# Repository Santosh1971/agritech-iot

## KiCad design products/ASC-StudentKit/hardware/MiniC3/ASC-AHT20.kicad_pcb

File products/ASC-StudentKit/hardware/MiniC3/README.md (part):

# ASC Mini-C3 rev B: the low-cost Mini, shared with FG1

This is the cost-down Mini for the ASC Student Kit (2026-10-10). The same board is meant to become the next **FG1 (FlowGuard)**: it has FG1's flow input, relay, RTC and LEDs. It does not replace rev A (`../Mini`, ESP32-S3 module, 97 × 47 mm).

Two boards share one 100 × 100 order:

| Board | Size | What it is |
|---|---|---|
| **ASC-MiniC3** | 48 × 44 mm | Carrier for a plug-in ESP32-C3 Super Mini. It has a flow input, a 5 V pump driver, a 230 V relay, a DS1307 RTC, I2C and AUX terminals and four LEDs. |
| **ASC-AHT20** | 48 × 6 mm | A T/RH "sensor stick" on a 4-core cable, so the sensor sits outside the box and students can breathe on it |

**The panel (`fab/ASC-MiniC3-panel-gerbers.zip`, 98 × 98 mm, order this one):**
- It holds 4 Minis (2 × 2) and **2 sticks** underneath. FG1 builds don't need a stick.
- **No V-cut.** JLC charges extra for V-cut, so WhyPCB asked for routed slots instead.
- The boards are separated by **2 mm routed slots**, drawn as closed cut-outs in the board outline.
- The slots stop short at the panel edges and around the slot crossings, leaving small **plain tabs**: about 2 mm at the edges and 5 mm at the crossings.
- **No mouse bites:** WhyPCB says JLC may not accept them. To set them back, change `MOUSE_BITES` in `tools/panel.py`. Break the tabs with pliers or a nibbler and file the stubs flush.
- The zip also carries `ASC-MiniC3-panel-drawing.pdf` and `PANEL-README.txt` for the fab.
- Copper keeps ≥ 0.4 mm from every edge.
- **Price** (WhyPCB): ₹1,500 for 5 panels or ₹2,000 for 10, which is ₹50 per Mini at 10 panels. 98 × 98 stays inside their 100 × 100 price; they also accept up to 102 × 100.

## Status

| Item | State |
|---|---|
| Schematics | Both are generated from `tools/design.py` and `tools/design_aht20.py`. **ERC: 0 errors, 0 warnings** on both. |
| PCBs | Both are routed (Freerouting) with zones filled. **DRC at every severity: 0 violations, 0 unconnected, schematic parity clean** on both (kicad-cli 9.0.7). The panel's DRC shows 0 errors. |
| 230 V | **5.3 mm** measured from relay copper to anything else. The DRC rule in `ASC-MiniC3.kicad_dru` requires ≥ 5 mm. Inside the relay, coil and contacts are 9.6 mm apart. |
| Fab | Panel, Mini and stick Gerbers. JLC BOM/CPL for each board and for the panel (unique designators R1_1 … R1_4). Schematic PDFs, 1:1 prints and renders. Run `tools/fab.sh` to regenerate. |
| Costing | `costing.csv`: board plus stick about ₹267, full kit about ₹1,026 (IP-65-26, YF-S401 at ₹230, HF46F at ₹42, 3 standoffs) |
| Mounting | 3 × 4.2 mm holes, arranged in a triangle, for 5 mm nylon reverse-mount snap standoffs (Probots PRO5803, ₹9.40 at 50+). Each standoff's flat base sticks to the box floor with double-sided foam tape; the snap head goes through the PCB hole. This works in any box with a flat floor; the box's own bosses are not used. Enclosure: REI IP-65-26 (90 × 58 × 44). |

## 3D models

Our own parts have no 3D models in KiCad's library (the Phoenix terminals, the MSTBVA header and the JST-XH do). `tools/gen_3d.py` writes simple coloured STEP models for them into `ASC.3dshapes/` (boxes and cylinders sized from the datasheets):
- the Super Mini on its sockets;
- the tabbed CR2032 and the HF46F relay;
- the AHT20 and the snap standoffs (the standoffs show below the board).

`tools/apply_3d.py` attaches them to the routed boards without re-routing; `gen_pcb.py` and `panel.py` attach them automatically. `fab/ASC-MiniC3.step` and `fab/ASC-AHT20.step` are full board assemblies, for checking the fit in the enclosure.

## Pin map (ESP32-C3 Super Mini)

| GPIO | Function | Notes |
|---|---|---|
| IO0, IO1 | AUX A0, A1 | ADC1 inputs |
| IO3 | PUMP | ULN2003A channels 1 + 2 in parallel (about 0.9 V drop, so ~4 V at the pump). Off through reset. |
| IO4 | AUX D | 10 k pull-up. For DHT11/22 or a DS18B20 probe. |
| IO5 | FLOW | YF-S401 (5880 pulses per litre) or YF-S201 (450 per litre). Level-shifted by D2 + R6. |
| IO6, IO7 | SDA, SCL | DS1307 (0x68) and AHT20 (0x38). 4.7 k pull-ups to 3V3. |
| IO10 | STATUS LED | FG1 uses it as the WiFi/status LED |
| IO20 | RELAY | ULN2003A channel 3. This pin is UART0 RX, an input at boot, so the relay stays off while the board boots. ULN2003A inputs 4–7 are grounded, outputs 4–7 free. |
| IO2, IO8, IO9, IO21 | free | IO2/8/9 are strapping pins (IO8 = module LED, IO9 = BOOT). IO21 is UART0 TX. |

## Connectors

| Ref | Connector | Pins |
|---|---|---|
| J5 | I2C, 4-pole 3.5 mm screw terminal (top edge) | 3V3, GND, SCL, SDA. This is the AHT20 stick's order and the usual VIN GND SCL SDA module order. |
| J4 | FLOW (top right): one footprint, fit **either** a JST-XH 3-pin header (student bench: takes the YF-S401 plug) **or** a 3-pole 3.5 mm screw terminal (FG1 / field: long cable). | 5V (red), GND (black), SIG (yellow); silkscreen reads S G 5V, left to right |
| J3 | AUX, 5-pole 3.5 mm screw terminal (bottom edge) | 3V3, D, A0, A1, GND |
| J1 | PUMP, 2-pole 3.5 mm screw terminal (bottom edge) | P+ (5 V), P− (low side) |
| J6 | RELAY 230 V, pluggable 5.08 mm 2-pole MSTBVA header + plug (bottom right), the same family as FG1's relay connector | NO, COM. HF46F, 5 A 250 VAC, for a pump contactor coil. |

## Assembly markings (for hand soldering)

House style, as on the WPC and FG1 boards:
- **Labels:** every part has its reference and value on the top silkscreen: `R3 1K`, `R5 470E`, `U3 ULN2003`, `C1 220U`, `D3 YEL` and so on. R8 and R9 share one label, `R8 R9 4K7`.
- **Big parts:** the relay and coin-cell labels sit inside their outlines, where the part goes.
- **Pin 1:** a **1** marks pin 1 of each IC (U2 DS1307, U3 ULN2003, the AHT20).
- **Anodes:** a **+** marks the anode of every LED and of D2.
- **LED colours:** PUMP and RLY yellow, STATUS red, FLOW yellow-green. FLOW runs from 3.3 V, too low for an emerald green LED. The Super Mini's own blue LED (GPIO8) is the WiFi-status LED in firmware. The electrolytic and the coin cell carry their own + marks.
- **LED size:** the LEDs are **1206** (bigger pads, as on WPC).
- **Back:** "ASC Mini-C3 rev B / Agri Sensors and Controls Oct 2026".

`gen_pcb.py` places the labels automatically, clear of pads, part bodies and each other (`ASSEMBLY_VALUE`, `LABEL_INSIDE` and `MARKS` in the design file). The LED block is laid out by hand in `silk()`.

## LEDs (seen through the clear lid)

| LED | How it's driven |
|---|---|
| PUMP (red) | Hardware: on the pump driver |
| FLOW (yellow) | Hardware: blinks with every flow pulse |
| STATUS (green) | GPIO10 |
| RELAY (blue) | Hardware: across the relay coil |

## Moving FG1 onto this board

1. **Firmware.** FG1 runs on a classic ESP32 today (`esp32dev`). It needs a C3 build with these pins: RELAY IO20, FLOW IO5, I2C IO6/IO7, status LED IO10.
2. **Flow LED.** It no longer needs a GPIO, so FG1's `FLOW_SENSOR_LED_PIN` goes away.
3. **Flow sensor.** Set `DEFAULT_PULSES_PER_LITER` to suit the sensor: 450 for a YF-S201, 5880 for a YF-S401.
4. **Power.** In the field, FG1 runs from a 5 V / 1 A USB-C charger plugged into the Super Mini.
5. **Relay.** The relay is an HF46F (5 A), not FG1's SRD (10 A). That is ample for a contactor coil. The SRD's COM pin sits between its two coil pins, which made 5 mm clearance impossible on a 48 mm board.

## Check before ordering

1. **Super Mini footprint.** Print `fab/ASC-MiniC3-print-1to1.pdf` at 100 % and lay a real Super Mini on it. The rows should be 15.24 mm apart. The silkscreen marks IO5 and 5V at the USB end and IO21 and IO0 at the far end, so a mirrored module is easy to see.
2. **Tabbed CR2032.** The two + legs are 15.2 mm apart. The − leg offset of 4.0 mm is a guess, so measure one cell.
   - **Alternative:** a replaceable cell in a CR2032 holder ([Rajiv Electronics](https://rajivelectronics.com/product/cr2032-3v-pcb-mount-vertical-battery-holder), ₹11.80).
   - The Rajiv holder (photo, SKU RBH-2) is a vertical holder with **3 pins**. A different holder's datasheet shows 2 pins 20.0 mm apart, so the layout varies by maker.
   - Its pin positions may or may not match the tabbed cell's pads. **Measure a sample before ordering.**
   - If they differ, its pads can be added next to the tabbed cell's, the same way the flow connector takes either part.
3. **YF-S401 plug order.** The board expects 5V (red) on pin 1, GND (black) in the middle and SIG (yellow) on pin 3. This follows AM Electronics' listing and photo. Check one plug: red must land on the pin next to the 5V label.
4. **HF46F footprint.** It is the same footprint as rev A (Hongfa datasheet). Push a real relay through a 1:1 print.
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
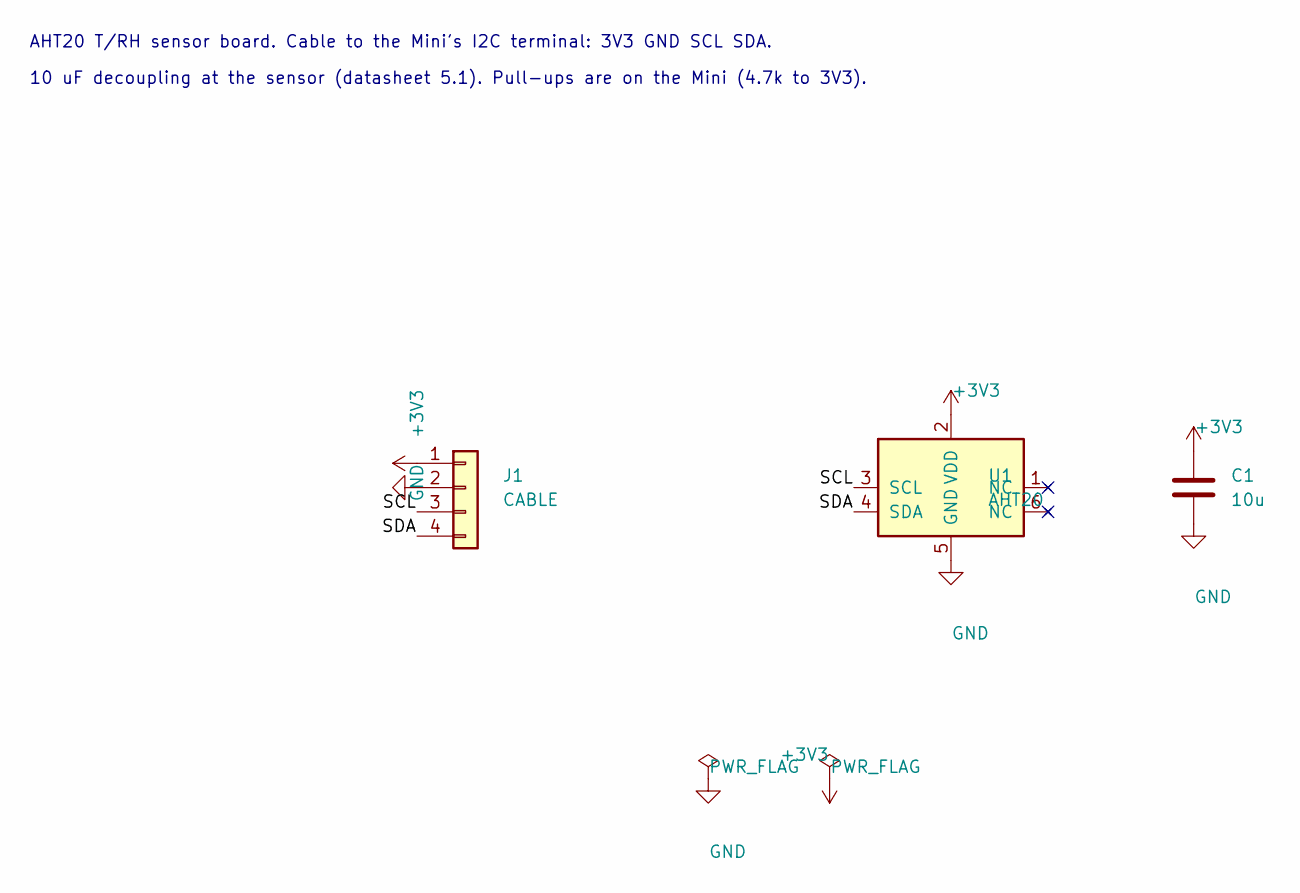
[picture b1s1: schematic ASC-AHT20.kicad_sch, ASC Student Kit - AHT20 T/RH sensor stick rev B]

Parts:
C1: 10u; C_0805_2012Metric
J1: CABLE; PinHeader_1x04_P2.54mm_Vertical
U1: AHT20; Aosong_AHT20_DFN-6_3x3mm

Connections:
+3V3: C1.1, J1.1, U1.2 (VDD)
/SCL: J1.3, U1.3 (SCL)
/SDA: J1.4, U1.4 (SDA)
GND: C1.2, J1.2, U1.5 (GND)

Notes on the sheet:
AHT20 T/RH sensor board. Cable to the Mini's I2C terminal: 3V3 GND SCL SDA.
10 uF decoupling at the sensor (datasheet 5.1). Pull-ups are on the Mini (4.7k to 3V3).

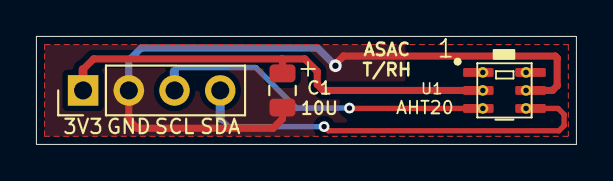
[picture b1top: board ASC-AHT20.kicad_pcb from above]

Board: 2 copper layers, 30.0 x 6.0 mm, 3 parts (0 on the bottom side), 4 nets.

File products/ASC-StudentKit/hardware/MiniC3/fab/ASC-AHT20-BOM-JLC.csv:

Comment,Designator,Footprint,LCSC Part #
10u,C1,C_0805_2012Metric,C15850
AHT20,U1,Aosong_AHT20_DFN-6_3x3mm,C2757850

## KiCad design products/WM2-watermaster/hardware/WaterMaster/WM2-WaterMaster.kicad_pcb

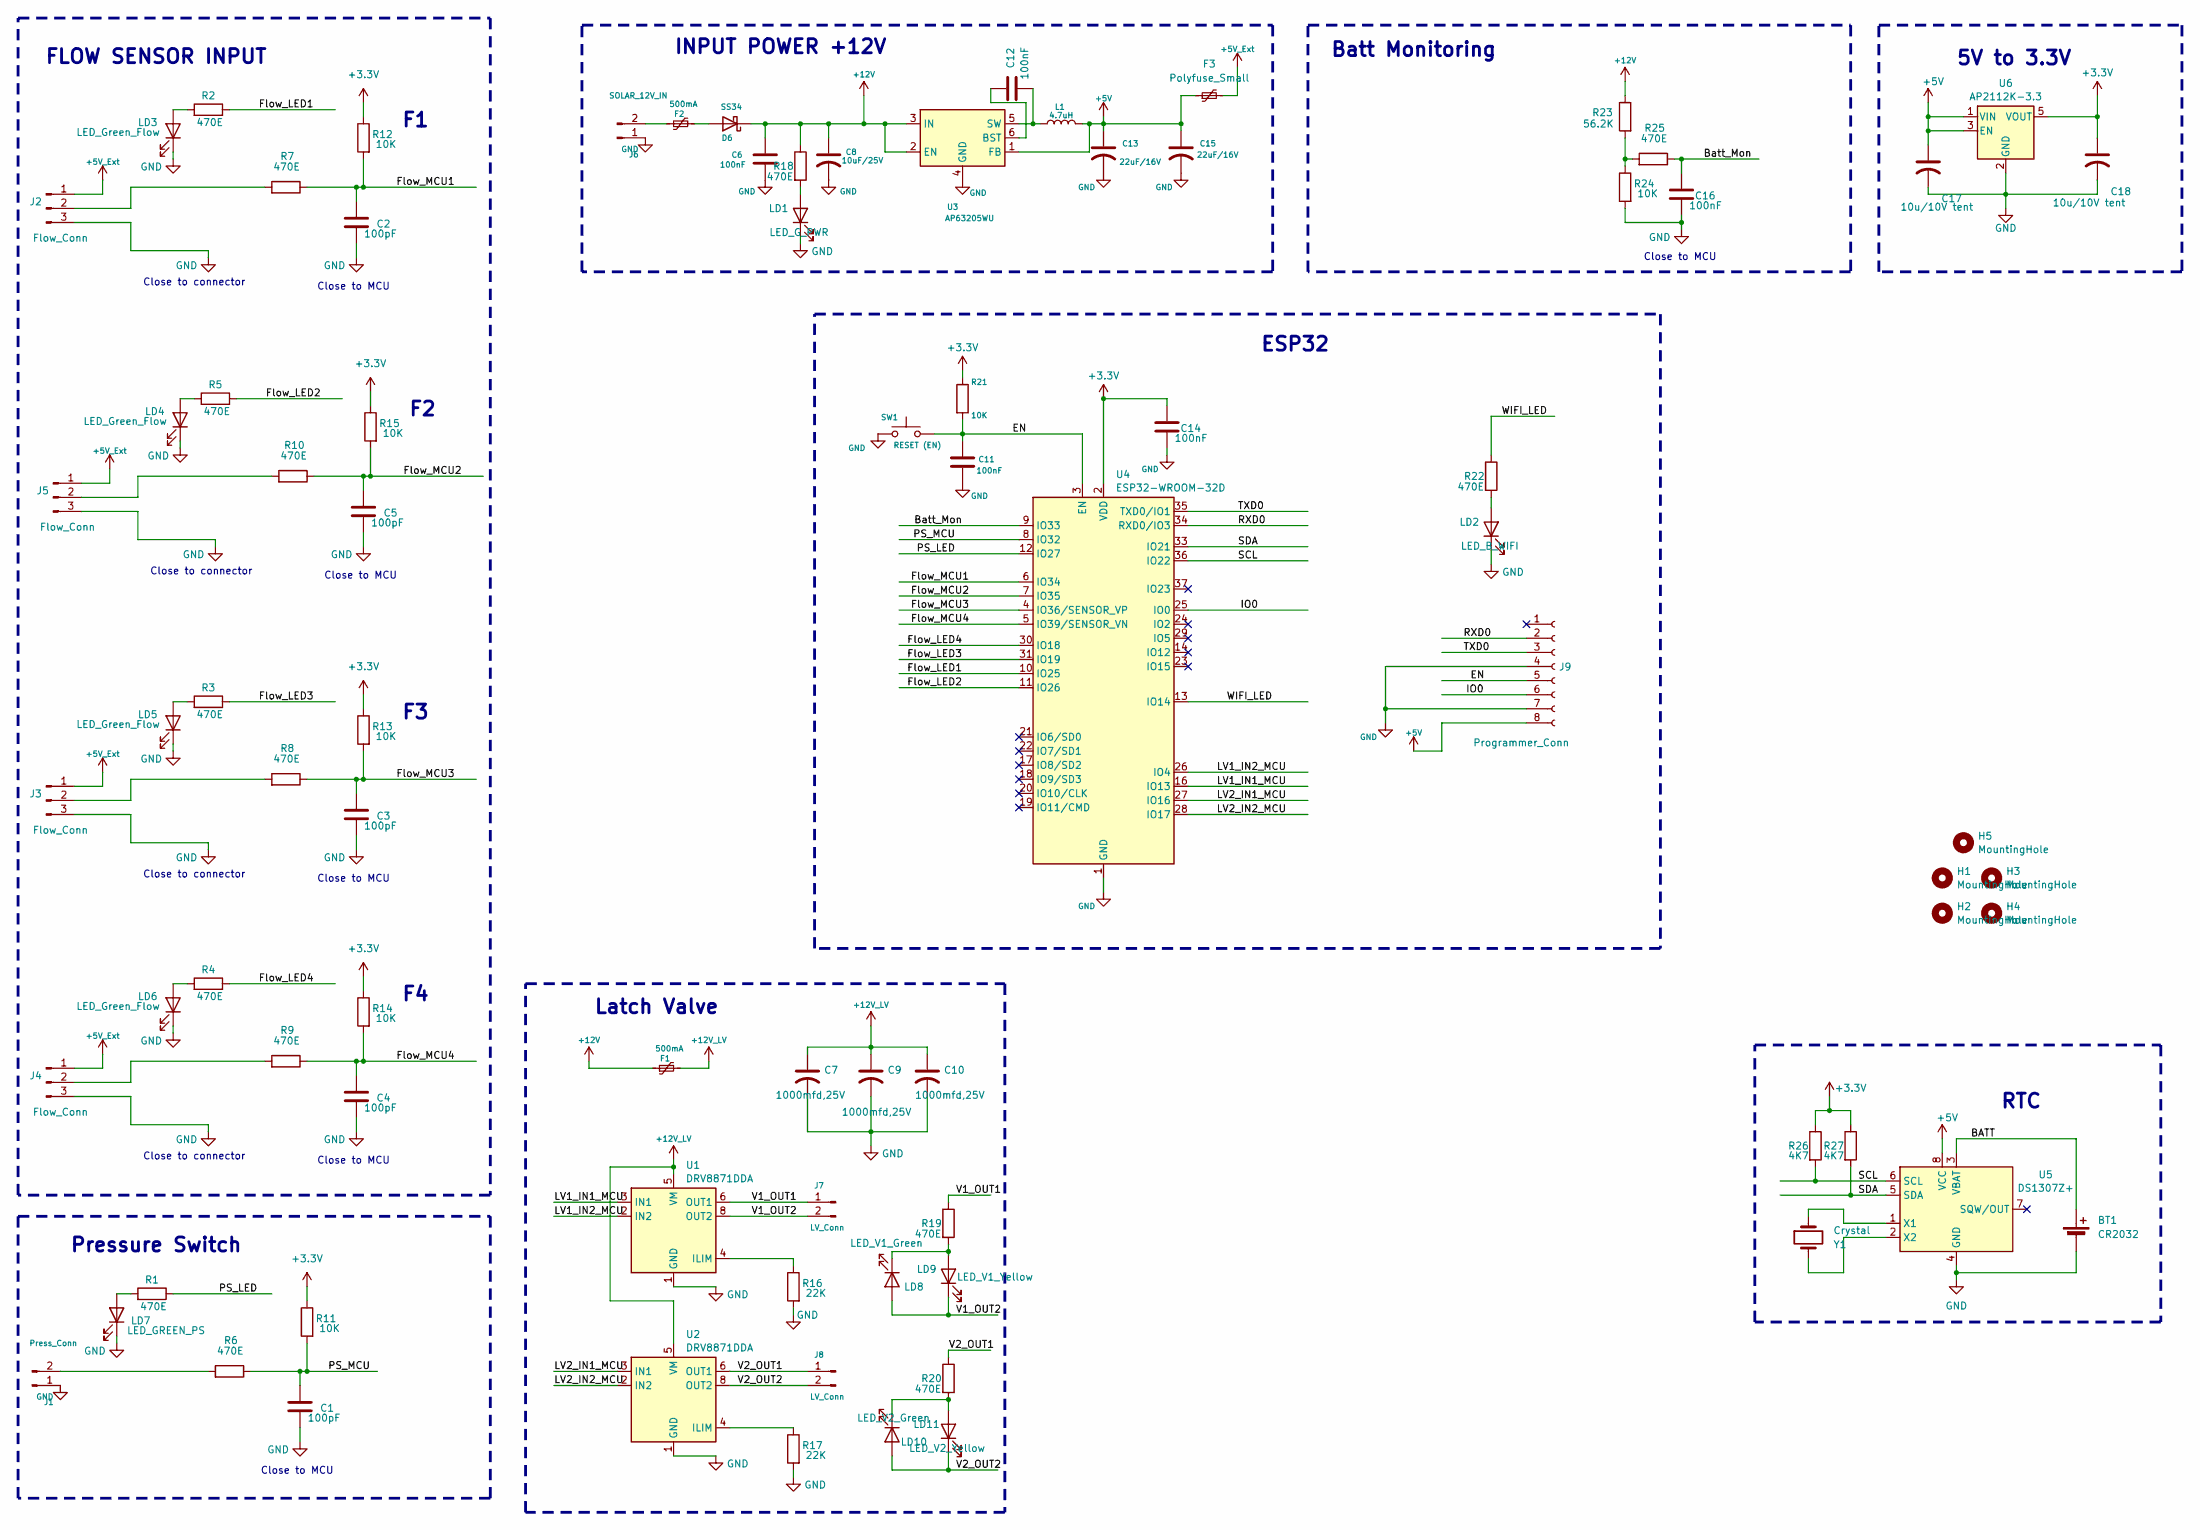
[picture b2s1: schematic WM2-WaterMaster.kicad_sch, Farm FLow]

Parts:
BT1: CR2032; BatteryHolder_MYOUNG_BS-07-A1BJ001_CR2032
C1, C2, C3, C4, C5: 100pF; C_0805_2012Metric
C6, C11, C12, C14, C16: 100nF; C_0805_2012Metric
C7, C9, C10: 1000mfd,25V; CP_Radial_D10.0mm_P2.50mm_P5.00mm
C8: 10uF/25V; C_1206_3216Metric_Pad1.33x1.80mm_HandSolder
C13, C15: 22uF/16V; C_1206_3216Metric_Pad1.33x1.80mm_HandSolder
C17, C18: 10u/10V tent; C_0805_2012Metric
D6: SS34; D_SMA
F1, F2: 500mA; L_1206_3216Metric
F3: Polyfuse_Small; L_1206_3216Metric
H1, H2, H3, H4, H5: MountingHole; MountingHole_4.5mm
J1: Press_Conn; PhoenixContact_MSTBA_2,5_2-G-5,08_1x02_P5.08mm_Horizontal
J2, J3, J4, J5: Flow_Conn; PhoenixContact_MSTBVA_2,5_3-G-5,08_1x03_P5.08mm_Vertical
J6: SOLAR_12V_IN; PhoenixContact_MSTBA_2,5_2-G-5,08_1x02_P5.08mm_Horizontal
J7, J8: LV_Conn; PhoenixContact_MSTBA_2,5_2-G-5,08_1x02_P5.08mm_Horizontal
J9: Programmer_Conn; JST_XH_B8B-XH-AM_1x08_P2.50mm_Vertical
L1: 4.7uH; L_Neosid_Ms85T
LD1: LED_G_PWR; C_1206_3216Metric
LD2: LED_B_WIFI; C_1206_3216Metric
LD3, LD4, LD5, LD6: LED_Green_Flow; C_1206_3216Metric
LD7: LED_GREEN_PS; C_1206_3216Metric
LD8: LED_V1_Green; C_1206_3216Metric
LD9: LED_V1_Yellow; C_1206_3216Metric
LD10: LED_V2_Green; C_1206_3216Metric
LD11: LED_V2_Yellow; C_1206_3216Metric
R1, R2, R3, R4, R5, R6, R7, R8, R9, R10, R18, R19, R20, R22, R25: 470E; R_0805_2012Metric
R11, R12, R13, R14, R15, R21, R24: 10K; R_0805_2012Metric
R16, R17: 22K; R_0805_2012Metric
R23: 56.2K; R_0805_2012Metric
R26, R27: 4K7; R_0805_2012Metric
SW1: RESET (EN); SW_Tactile_SPST_NO_Straight_CK_PTS636Sx25SMTRLFS
U1, U2: DRV8871DDA; Texas_HTSOP-8-1EP_3.9x4.9mm_P1.27mm_EP2.95x4.9mm_Mask2.4x3.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
U3: AP63205WU; TSOT-23-6
U4: ESP32-WROOM-32D
U5: DS1307Z+; SOIC-8_3.9x4.9mm_P1.27mm
U6: AP2112K-3.3; SOT-23-5
Y1: Crystal; Crystal_C38-LF_D3.0mm_L8.0mm_Horizontal

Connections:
+3.3V: C14.1, C18.1, R11.1, R12.1, R13.1, R14.1, R15.1, R21.1, R26.1, R27.1, U4.2 (VDD), U6.5 (VOUT)
+5V: C13.1, C15.1, C17.1, F3.1, J9.8, L1.2, U3.1 (FB), U5.8 (VCC), U6.1 (VIN), U6.3 (EN)
+5V_Ext: F3.2, J2.1, J3.1, J4.1, J5.1
+12V: C6.1, C8.1, D6.1 (K), F1.1, R18.1, R23.1, U3.2 (EN), U3.3 (IN)
+12V_LV: C7.1, C9.1, C10.1, F1.2, U1.5 (VM), U2.5 (VM)
/BATT: BT1.1 (+), U5.3 (VBAT)
/Batt_Mon: C16.1, R25.1, U4.9 (IO33)
/EN: C11.1, J9.5, R21.2, SW1.1, U4.3 (EN)
/Flow_LED1: R2.1, U4.10 (IO25)
/Flow_LED2: R5.1, U4.11 (IO26)
/Flow_LED3: R3.1, U4.31 (IO19)
/Flow_LED4: R4.1, U4.30 (IO18)
/Flow_MCU1: C2.1, R7.1, R12.2, U4.6 (IO34)
/Flow_MCU2: C5.1, R10.1, R15.2, U4.7 (IO35)
/Flow_MCU3: C3.1, R8.1, R13.2, U4.4 (IO36/SENSOR_VP)
/Flow_MCU4: C4.1, R9.1, R14.2, U4.5 (IO39/SENSOR_VN)
/IO0: J9.6, U4.25 (IO0)
/LV1_IN1_MCU: U1.3 (IN1), U4.16 (IO13)
/LV1_IN2_MCU: U1.2 (IN2), U4.26 (IO4)
/LV2_IN1_MCU: U2.3 (IN1), U4.27 (IO16)
/LV2_IN2_MCU: U2.2 (IN2), U4.28 (IO17)
/PS_LED: R1.1, U4.12 (IO27)
/PS_MCU: C1.1, R6.1, R11.2, U4.8 (IO32)
/RXD0: J9.2, U4.34 (RXD0/IO3)
/SCL: R26.2, U4.36 (IO22), U5.6 (SCL)
/SDA: R27.2, U4.33 (IO21), U5.5 (SDA)
/TXD0: J9.3, U4.35 (TXD0/IO1)
/V1_OUT1: J7.1, R19.1, U1.6 (OUT1)
/V1_OUT2: J7.2, LD8.2 (A), LD9.1 (K), U1.8 (OUT2)
/V2_OUT1: J8.1, R20.1, U2.6 (OUT1)
/V2_OUT2: J8.2, LD10.2 (A), LD11.1 (K), U2.8 (OUT2)
/WIFI_LED: R22.1, U4.13 (IO14)
GND: BT1.2 (-), C1.2, C2.2, C3.2, C4.2, C5.2, C6.2, C7.2, C8.2, C9.2, C10.2, C11.2, C13.2, C14.2, C15.2, C16.2, C17.2, C18.2, J1.1, J2.3, J3.3, J4.3, J5.3, J6.1, J9.4, J9.7, LD1.1 (K), LD2.1 (K), LD3.1 (K), LD4.1 (K), LD5.1 (K), LD6.1 (K), LD7.1 (K), R16.2, R17.2, R24.2, SW1.2, U1.1 (GND), U1.7 (GND), U1.9 (GND), U2.1 (GND), U2.7 (GND), U2.9 (GND), U3.4 (GND), U4.1 (GND), U4.15 (GND), U4.38 (GND), U4.39 (GND), U5.4 (GND), U6.2 (GND)
unnamed: D6.2 (A), F2.2
unnamed: J1.2, R6.2
unnamed: J2.2, R7.2
unnamed: J3.2, R8.2
unnamed: J4.2, R9.2
unnamed: J5.2, R10.2
unnamed: F2.1, J6.2
unnamed: LD1.2 (A), R18.2
unnamed: LD2.2 (A), R22.2
unnamed: LD3.2 (A), R2.2
unnamed: LD4.2 (A), R5.2
unnamed: LD5.2 (A), R3.2
unnamed: LD6.2 (A), R4.2
unnamed: LD7.2 (A), R1.2
unnamed: LD8.1 (K), LD9.2 (A), R19.2
unnamed: LD10.1 (K), LD11.2 (A), R20.2
unnamed: R23.2, R24.1, R25.2
unnamed: R16.1, U1.4 (ILIM)
unnamed: R17.1, U2.4 (ILIM)
unnamed: C12.1, U3.6 (BST)
unnamed: C12.2, L1.1, U3.5 (SW)
unnamed: U5.1 (X1), Y1.1
unnamed: U5.2 (X2), Y1.2

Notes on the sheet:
RTC
INPUT POWER +12V
Close to MCU
ESP32
Close to connector
Latch Valve
Pressure Switch
FLOW SENSOR INPUT
5V to 3.3V
Batt Monitoring

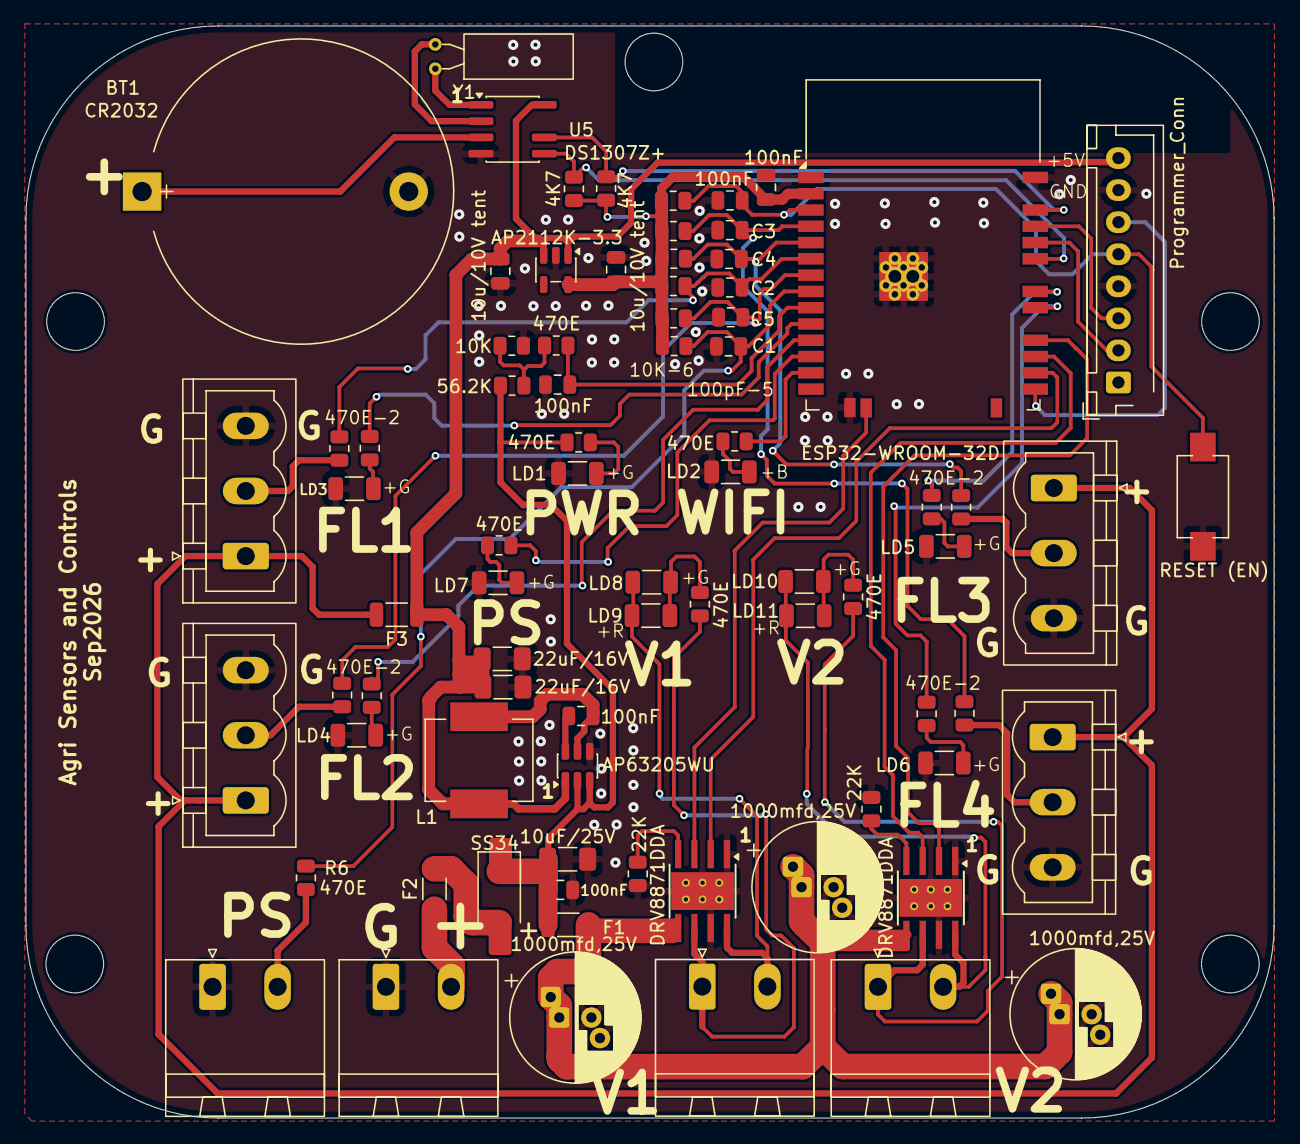
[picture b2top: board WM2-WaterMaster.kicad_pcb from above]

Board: 2 copper layers, 97.4 x 85.2 mm, 84 parts (0 on the bottom side), 56 nets.

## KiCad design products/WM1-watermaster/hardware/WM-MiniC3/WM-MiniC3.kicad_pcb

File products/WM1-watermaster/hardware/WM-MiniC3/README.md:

# WM-Mini C3 rev A: pump, doser and 4-valve controller (2026-10-27)

A larger FG1. An ESP32-C3 Super Mini (plug-in, USB-C powered) drives six SRD relays through a ULN2003A:
- **K1 PUMP** and **K2 DOSER** switch 230 V.
- **K3–K6** switch 12/24 VAC valves, with one common.

It also has a Hall flow input, a DS1307 RTC with a CR2032, and seven LEDs. The plan and the decisions behind it are in [SPEC.md](SPEC.md) (draft 0.3) and on the "WM-Mini C3 Plan" page.

## Status

| Item | State |
|---|---|
| Schematic | Generated from `tools/design.py`, with wires inside each block and labels only between blocks. **ERC: 0 errors, 0 warnings.** |
| PCB | 99 × 48 mm, 2 layers. Routed with Freerouting, zones filled. **DRC at every severity: 0 violations, 0 unconnected, schematic parity clean** (kicad-cli 9.0.7). |
| 230 V | 5 mm from the pump/doser copper (including their NC pins, which are live while off) to all other copper, enforced by `WM-MiniC3.kicad_dru`. The exceptions are inside K1/K2: 3.5 mm to their own coil pins (the SRD's pinout gives 3.6 mm), and 2.4 mm between pump and doser (the 5.08 mm header has 2.48 mm between its own pads). |
| Panel | `panel/WM-MiniC3-panel.kicad_pcb`, 99 × 98 mm: 2 boards and a 2 mm routed slot with 3 plain tabs (no V-cut, no mouse bites). Board 1 is turned 180°, so both connector edges face outwards. |
| Fab | `fab/`: panel and board Gerbers, schematic PDF, 1:1 prints (top and bottom), BOM, STEP and renders. **Order `WM-MiniC3-panel-gerbers.zip`.** |

## Layout

The board is the draft 0.3 plan **mirrored left to right**. On an upright SRD the NO pin comes out on the left. With the 230 V corner on the left, the pump and doser NO and COM run straight down into their headers without crossing, and still keep 5 mm from the valve header.

- **Bottom left:** K1 PUMP and K2 DOSER, upright, directly above J2 and J3.
- **Top left, above the relays they drive (all > 5 mm from 230 V):**
  - the ULN2003;
  - the six relay LEDs (P D V1 V2 V3 V4) and their resistors;
  - C1, 1000 µF / 16 V (10 mm, 5 mm pitch).
- **Middle, valve block:**
  - K3 V1 and K4 V2 are inverted at the top edge.
  - K5 V3 and K6 V4 are upright below them.
  - All coils meet near the centre line.
- **Top right, next to the ESP:**
  - the CR2032 standing vertical;
  - the DS1307, a through-hole C26 crystal and the I2C pull-ups;
  - the FLOW LED and test pad TP1.
- **Bottom right:** the Super Mini, with USB-C at the bottom edge. Under the module sit the flow-input parts (B5819W, SLCESDB5V0D5 bidirectional 5 V TVS, SOD-523 on hand-solder pads, 10k). IO2 is unused (the AUX pull-up and test pad were removed).
- **+5 V:** 1 mm tracks from the module to all relay coils.
- **Bottom edge, left to right:** J2 PUMP (NO, COM), J3 DOSER (NO, COM), J4 VALVES (COM, V1, V2, V3, V4), J1 FLOW (5V, GND, SIG), USB-C.
- **Holes:** 2 × M3 at (3.5, 24) and (95.5, 24), 92 mm apart, as on the ESP32 test jig.

## Pin map

| GPIO | Net | Function |
|---|---|---|
| IO20 | RLY_PUMP | K1 pump, ULN in 6 / out 11 |
| IO10 | RLY_DOSER | K2 doser, ULN in 5 / out 12 |
| IO1 | RLY_V1 | K5 valve 1, ULN in 4 / out 13, LED D6 |
| IO0 | RLY_V2 | K3 valve 2, ULN in 1 / out 16, LED D7 |
| IO3 | RLY_V3 | K4 valve 3, ULN in 2 / out 15, LED D8 |
| IO4 | RLY_V4 | K6 valve 4, ULN in 3 / out 14, LED D9 |
| IO2 | — | unused (strapping pin, left floating as on Mini-C3) |
| IO5 | FLOW | flow pulses |
| IO6 / IO7 | SDA / SCL | DS1307 |
| IO21 | LED_FLOW | flow LED |
| IO8 | — | on-module LED = WiFi LED |
| IO9 | — | BOOT button = setup button |

## Parts that are not stock KiCad (`ASC.pretty`)

| Part | Footprint |
|---|---|
| Pluggable headers | `Pluggable_2EDGR_5.08_1x0{2,3,5}_Horizontal`: the stackable market header (2EDGR / KF2EDGR), body n × 5.08 mm. It has MSTBA pitch and drills, with round 2.6 mm pads. The pin row is 2.5 mm from the edge; the plug overhangs the board edge. |
| Relays | `Relay_SPDT_SANYOU_SRD_Outline`: KiCad's SRD Form C with the silkscreen cut to the outline, so the K1 PUMP etc. labels fit inside |
| Super Mini | `ESP32-C3_SuperMini_Socket`: from ASC Mini-C3, without its outline silk (that ran past the board edge) |
| CR2032 | `Battery_CR2032_Vertical_3pin`: from ASC Mini-C3 |
| Flow TVS | `D_SOD-523_HandSolder`: SOD-523 with 1.2 × 1.0 mm pads at 2.0 mm pitch for hand soldering (SLKOR SLCESDB5V0D5) |

## Check before ordering

1. **Print `fab/WM-MiniC3-print-1to1.pdf` at 100 %.** Lay on it a real SRD relay, a 2EDGR header, the CR2032 holder and the Super Mini. Pin sides: IO5 and 5V must be at the USB end.
2. **SRD NO pin.** Pad 3 is NO, as on WM1. Check one Rajiv relay (RERL-32) with a meter.
3. **CR2032 holder pins.** The footprint is the Mini-C3 tabbed-cell layout, and its − leg position is provisional. Measure the RBH-2 holder.
4. **C1 size.** The footprint is 10 mm diameter, 5 mm pitch: check your 1000 µF part.
5. **Plug overhang.** The plugs stick out about 8 mm past the bottom edge. Check this against the box wall.
6. **The Super Mini plugs in after the board is screwed down.** Its antenna end sits over the right M3 screw head; a DRC rule ignores that overlap on purpose.

## Regenerate

```bash
cd products/WM1-watermaster/hardware/WM-MiniC3
zsh tools/build.sh 5     # schematic + ERC, then place / route / DRC until clean (Freerouting is not deterministic)
zsh tools/fab.sh         # panel + fab/
```

`tools/clearance_check.py` and `tools/layout_svg.py` are the draft 0.3 planning helpers. They describe the unmirrored plan.

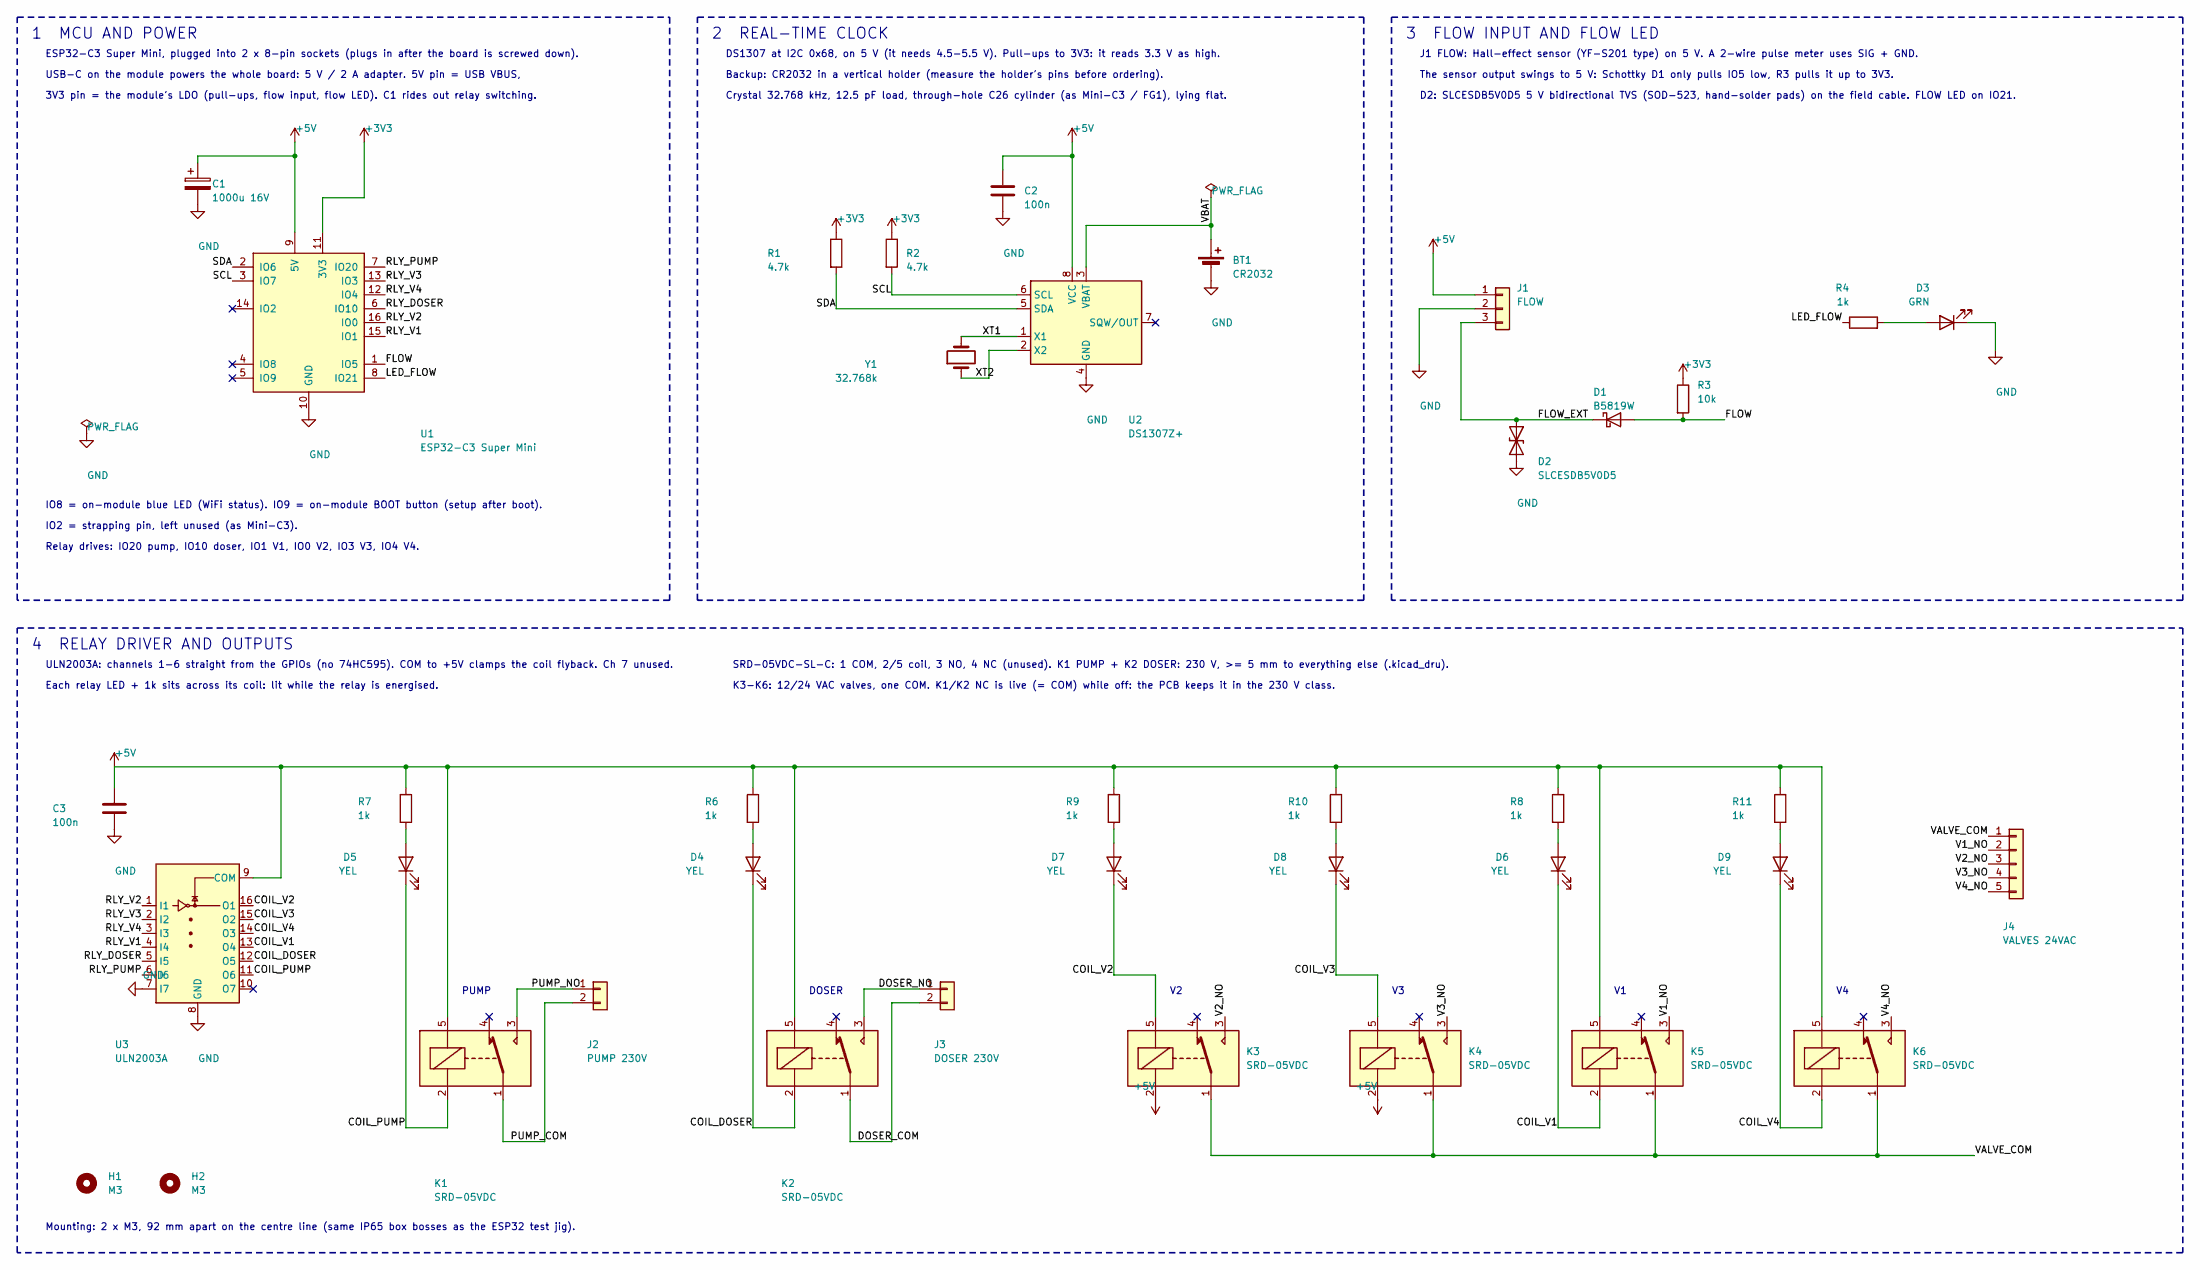
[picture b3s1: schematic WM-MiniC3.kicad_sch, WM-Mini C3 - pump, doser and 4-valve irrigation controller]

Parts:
BT1: CR2032; Battery_CR2032_Vertical_3pin
C1: 1000u 16V; CP_Radial_D10.0mm_P5.00mm
C2, C3: 100n; C_0805_2012Metric
D1: B5819W; D_SOD-123
D2: SLCESDB5V0D5; D_SOD-523_HandSolder
D3: GRN; LED_1206_3216Metric
D4, D5, D6, D7, D8, D9: YEL; LED_1206_3216Metric
H1, H2: M3; MountingHole_3.2mm_M3
J1: FLOW; Pluggable_2EDGR_5.08_1x03_Horizontal
J2: PUMP 230V; Pluggable_2EDGR_5.08_1x02_Horizontal
J3: DOSER 230V; Pluggable_2EDGR_5.08_1x02_Horizontal
J4: VALVES 24VAC; Pluggable_2EDGR_5.08_1x05_Horizontal
K1, K2, K3, K4, K5, K6: SRD-05VDC; Relay_SPDT_SANYOU_SRD_Outline
R1, R2: 4.7k; R_0805_2012Metric
R3: 10k; R_0805_2012Metric
R4, R6, R7, R8, R9, R10, R11: 1k; R_0805_2012Metric
U1: ESP32-C3 Super Mini; ESP32-C3_SuperMini_Socket
U2: DS1307Z+; SOIC-8_3.9x4.9mm_P1.27mm
U3: ULN2003A; SOIC-16_3.9x9.9mm_P1.27mm
Y1: 32.768k; Crystal_C26-LF_D2.1mm_L6.5mm_Horizontal

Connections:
+3V3: R1.1, R2.1, R3.1, U1.11 (3V3)
+5V: C1.1, C2.1, C3.1, J1.1, K1.5, K2.5, K3.2, K4.2, K5.5, K6.5, R6.1, R7.1, R8.1, R9.1, R10.1, R11.1, U1.9 (5V), U2.8 (VCC), U3.9 (COM)
/COIL_DOSER: D4.1 (K), K2.2, U3.12 (O5)
/COIL_PUMP: D5.1 (K), K1.2, U3.11 (O6)
/COIL_V1: D6.1 (K), K5.2, U3.13 (O4)
/COIL_V2: D7.1 (K), K3.5, U3.16 (O1)
/COIL_V3: D8.1 (K), K4.5, U3.15 (O2)
/COIL_V4: D9.1 (K), K6.2, U3.14 (O3)
/DOSER_COM: J3.2, K2.1
/DOSER_NO: J3.1, K2.3
/FLOW: D1.2 (A), R3.2, U1.1 (IO5)
/FLOW_EXT: D1.1 (K), D2.1 (A1), J1.3
/LED_FLOW: R4.1, U1.8 (IO21)
/PUMP_COM: J2.2, K1.1
/PUMP_NO: J2.1, K1.3
/RLY_DOSER: U1.6 (IO10), U3.5 (I5)
/RLY_PUMP: U1.7 (IO20), U3.6 (I6)
/RLY_V1: U1.15 (IO1), U3.4 (I4)
/RLY_V2: U1.16 (IO0), U3.1 (I1)
/RLY_V3: U1.13 (IO3), U3.2 (I2)
/RLY_V4: U1.12 (IO4), U3.3 (I3)
/SCL: R2.2, U1.3 (IO7), U2.6 (SCL)
/SDA: R1.2, U1.2 (IO6), U2.5 (SDA)
/V1_NO: J4.2, K5.3
/V2_NO: J4.3, K3.3
/V3_NO: J4.4, K4.3
/V4_NO: J4.5, K6.3
/VALVE_COM: J4.1, K3.1, K4.1, K5.1, K6.1
/VBAT: BT1.1 (+), U2.3 (VBAT)
/XT1: U2.1 (X1), Y1.2
/XT2: U2.2 (X2), Y1.1
GND: BT1.2 (-), C1.2, C2.2, C3.2, D2.2 (A2), D3.1 (K), J1.2, U1.10 (GND), U2.4 (GND), U3.7 (I7), U3.8 (GND)
unnamed: D3.2 (A), R4.2
unnamed: D4.2 (A), R6.2
unnamed: D5.2 (A), R7.2
unnamed: D6.2 (A), R8.2
unnamed: D7.2 (A), R9.2
unnamed: D8.2 (A), R10.2
unnamed: D9.2 (A), R11.2

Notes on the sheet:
ESP32-C3 Super Mini, plugged into 2 x 8-pin sockets (plugs in after the board is screwed down).
USB-C on the module powers the whole board: 5 V / 2 A adapter. 5V pin = USB VBUS,
3V3 pin = the module's LDO (pull-ups, flow input, flow LED). C1 rides out relay switching.
IO8 = on-module blue LED (WiFi status). IO9 = on-module BOOT button (setup after boot).
IO2 = strapping pin, left unused (as Mini-C3).
Relay drives: IO20 pump, IO10 doser, IO1 V1, IO0 V2, IO3 V3, IO4 V4.
DS1307 at I2C 0x68, on 5 V (it needs 4.5-5.5 V). Pull-ups to 3V3: it reads 3.3 V as high.
Backup: CR2032 in a vertical holder (measure the holder's pins before ordering).
Crystal 32.768 kHz, 12.5 pF load, through-hole C26 cylinder (as Mini-C3 / FG1), lying flat.
J1 FLOW: Hall-effect sensor (YF-S201 type) on 5 V. A 2-wire pulse meter uses SIG + GND.
The sensor output swings to 5 V: Schottky D1 only pulls IO5 low, R3 pulls it up to 3V3.
D2: SLCESDB5V0D5 5 V bidirectional TVS (SOD-523, hand-solder pads) on the field cable. FLOW LED on IO21.
ULN2003A: channels 1-6 straight from the GPIOs (no 74HC595). COM to +5V clamps the coil flyback. Ch 7 unused.
Each relay LED + 1k sits across its coil: lit while the relay is energised.
SRD-05VDC-SL-C: 1 COM, 2/5 coil, 3 NO, 4 NC (unused). K1 PUMP + K2 DOSER: 230 V, >= 5 mm to everything else (.kicad_dru).
K3-K6: 12/24 VAC valves, one COM. K1/K2 NC is live (= COM) while off: the PCB keeps it in the 230 V class.
PUMP
DOSER
Mounting: 2 x M3, 92 mm apart on the centre line (same IP65 box bosses as the ESP32 test jig).
1 MCU AND POWER
2 REAL-TIME CLOCK
3 FLOW INPUT AND FLOW LED
4 RELAY DRIVER AND OUTPUTS

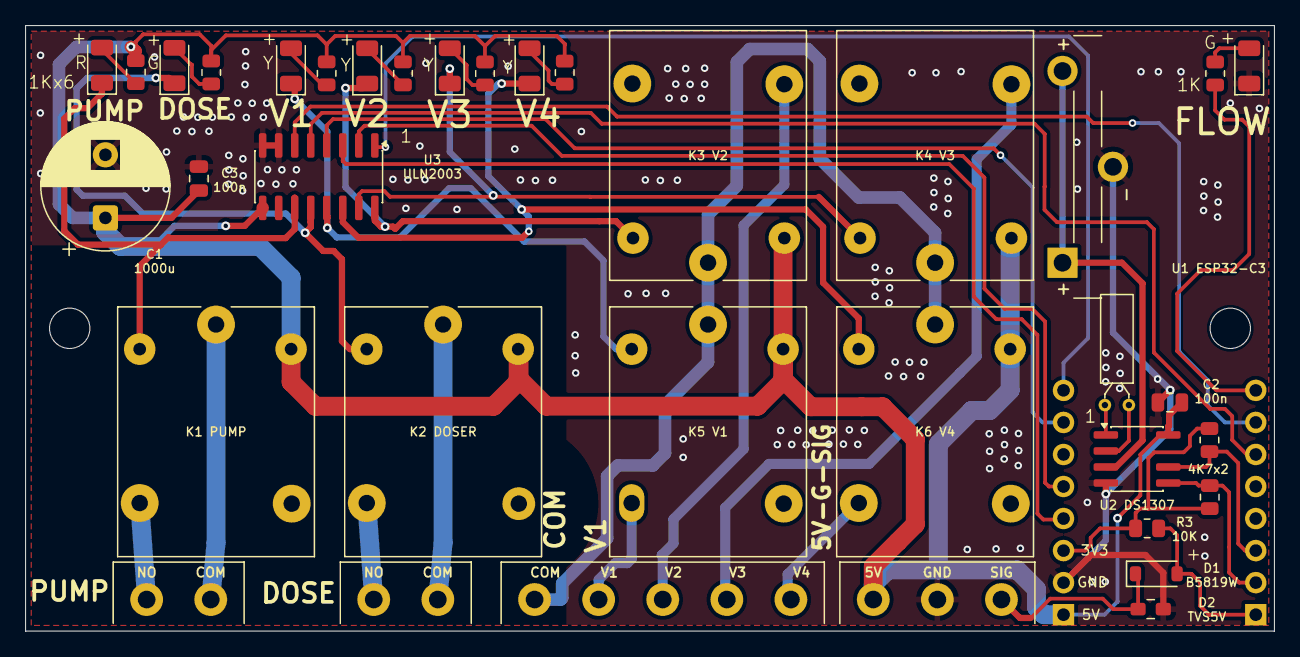
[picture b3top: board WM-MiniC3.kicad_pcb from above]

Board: 2 copper layers, 99.0 x 48.0 mm, 39 parts (0 on the bottom side), 39 nets.

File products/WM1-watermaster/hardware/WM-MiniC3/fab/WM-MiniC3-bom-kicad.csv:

"Reference","Value","Footprint","QUANTITY"
"BT1","CR2032","ASC:Battery_CR2032_Vertical_3pin","1"
"C1","1000u 16V","Capacitor_THT:CP_Radial_D10.0mm_P5.00mm","1"
"C2,C3","100n","Capacitor_SMD:C_0805_2012Metric","2"
"D1","B5819W","Diode_SMD:D_SOD-123","1"
"D2","SLCESDB5V0D5","ASC:D_SOD-523_HandSolder","1"
"D3","GRN","LED_SMD:LED_1206_3216Metric","1"
"D4-D9","YEL","LED_SMD:LED_1206_3216Metric","6"
"J1","FLOW","ASC:Pluggable_2EDGR_5.08_1x03_Horizontal","1"
"J2","PUMP 230V","ASC:Pluggable_2EDGR_5.08_1x02_Horizontal","1"
"J3","DOSER 230V","ASC:Pluggable_2EDGR_5.08_1x02_Horizontal","1"
"J4","VALVES 24VAC","ASC:Pluggable_2EDGR_5.08_1x05_Horizontal","1"
"K1-K6","SRD-05VDC","ASC:Relay_SPDT_SANYOU_SRD_Outline","6"
"R1,R2","4.7k","Resistor_SMD:R_0805_2012Metric","2"
"R3","10k","Resistor_SMD:R_0805_2012Metric","1"
"R4,R6-R11","1k","Resistor_SMD:R_0805_2012Metric","7"
"U1","ESP32-C3 Super Mini","ASC:ESP32-C3_SuperMini_Socket","1"
"U2","DS1307Z+","Package_SO:SOIC-8_3.9x4.9mm_P1.27mm","1"
"U3","ULN2003A","Package_SO:SOIC-16_3.9x9.9mm_P1.27mm","1"
"Y1","32.768k","Crystal:Crystal_C26-LF_D2.1mm_L6.5mm_Horizontal","1"

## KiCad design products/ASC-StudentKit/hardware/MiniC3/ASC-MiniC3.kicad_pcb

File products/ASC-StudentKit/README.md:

# ASC-StudentKit

These are the student kits (**Mini** and **Mega**) for the Student Product Studio (`docs/student-product-studio.md`). Each kit is a carrier board built on an ESP32-S3, plus starter modules and a ready-made enclosure. Agri Sensors and Controls supplies the kits to colleges, priced per batch.

The kits are also **Project #0** of the studio: they are designed by following the same stages a student follows.

- `docs/StudentKit_Specification_v0.1.md`: system specification with hardware, software and mechanical requirements. It is a draft, and the open decisions are listed in §8.
- `docs/StudentKit_Architecture_v0.1.md`: architecture (stage 3), covering block diagrams, pin map, connectors, power budget and battery life.
- `hardware/pinmap.json`: the pin map for both boards, checked by `python3 hardware/tools/check_pinmap.py`.
- `firmware/`: the ASC Studio firmware, one image for both kits and the DevKit stand-in. See `firmware/README.md` for the build and the serial protocol.
- `mobile-app/asc_studio_app/`: the shared ASC Studio phone app (Flutter, Android, spec §5A). It builds each student's screen from the layout in their design.

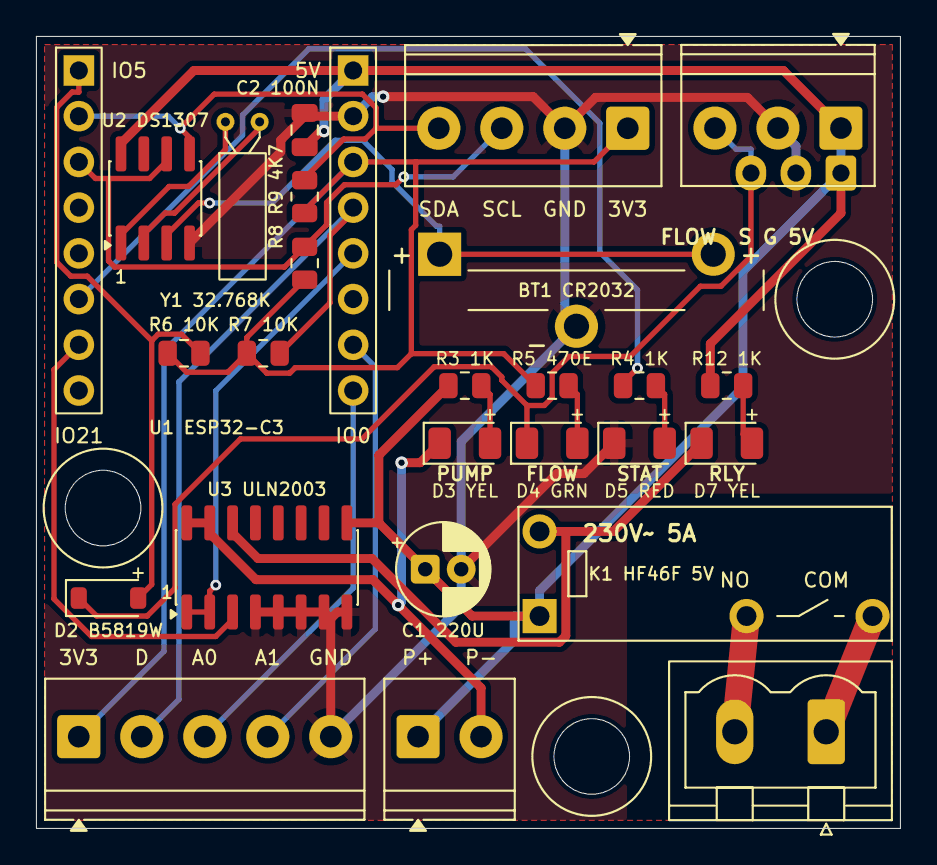
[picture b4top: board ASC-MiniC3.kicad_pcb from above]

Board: 2 copper layers, 48.0 x 44.0 mm, 29 parts (0 on the bottom side), 24 nets.

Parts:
BT1: CR2032 tabbed; Battery_CR2032_Vertical_3pin
C1: 220u 10V; CP_Radial_D5.0mm_P2.00mm
C2: 100n; C_0805_2012Metric
D2: B5819W; D_SOD-123
D3: PUMP yellow; LED_1206_3216Metric
D4: FLOW yellow-green; LED_1206_3216Metric
D5: STATUS red; LED_1206_3216Metric
D7: RELAY yellow; LED_1206_3216Metric
H1, H2, H3: SNAP 4.2; Snap_Standoff_4.2mm
J1: PUMP; TerminalBlock_Phoenix_PT-1,5-2-3.5-H_1x02_P3.50mm_Horizontal
J3: AUX; TerminalBlock_Phoenix_PT-1,5-5-3.5-H_1x05_P3.50mm_Horizontal
J4: FLOW (XH or 3.5 mm); Flow_XH3_or_PT-1,5-3-3.5mm
J5: I2C; TerminalBlock_Phoenix_PT-1,5-4-3.5-H_1x04_P3.50mm_Horizontal
J6: RELAY 230V (MSTBVA); PhoenixContact_MSTBVA_2,5_2-G-5,08_1x02_P5.08mm_Vertical
K1: HF46F/005-HS1; Relay_SPST_Hongfa_HF46F
R3, R4, R12: 1k; R_0805_2012Metric
R5: 470; R_0805_2012Metric
R6, R7: 10k; R_0805_2012Metric
R8, R9: 4.7k; R_0805_2012Metric
U1: ESP32-C3 Super Mini; ESP32-C3_SuperMini_Socket
U2: DS1307Z+; SOIC-8_3.9x4.9mm_P1.27mm
U3: ULN2003A; SOIC-16_3.9x9.9mm_P1.27mm
Y1: 32.768k 12.5pF; Crystal_C26-LF_D2.1mm_L6.5mm_Horizontal

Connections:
+3V3: J3.1, J5.1, R5.1, R6.1, R7.1, R8.1, R9.1, U1.11
+5V: C1.1, C2.1, J1.1, J4.1, K1.1, R3.1, R12.1, U1.9, U2.8, U3.9
/AUX_A0: J3.3, U1.16
/AUX_A1: J3.4, U1.15
/AUX_D: J3.2, R7.2, U1.12
/FLOW: D2.2, R6.2, U1.1
/FLOW_EXT: D2.1, D4.1, J4.3
/LED_FLOW_A: D4.2, R5.2
/LED_PUMP_A: D3.2, R3.2
/LED_RLY_A: D7.2, R12.2
/LED_STATUS: R4.1, U1.6
/LED_STATUS_A: D5.2, R4.2
/PUMP: U1.13, U3.1, U3.2
/PUMP_N: D3.1, J1.2, U3.15, U3.16
/RELAY: U1.7, U3.3
/RELAY_COIL: D7.1, K1.2, U3.14
/RELAY_COM: J6.1, K1.4
/RELAY_NO: J6.2, K1.3
/SCL: J5.3, R9.2, U1.3, U2.6
/SDA: J5.4, R8.2, U1.2, U2.5
/VBAT: BT1.1, U2.3
/XT1: U2.1, Y1.1
/XT2: U2.2, Y1.2
GND: BT1.2, C1.2, C2.2, D5.1, J3.5, J4.2, J5.2, U1.10, U2.4, U3.4, U3.5, U3.6, U3.7, U3.8

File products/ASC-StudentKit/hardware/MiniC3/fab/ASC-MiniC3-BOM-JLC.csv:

Comment,Designator,Footprint,LCSC Part #
100n,C2,C_0805_2012Metric,C49678
10k,"R6,R7",R_0805_2012Metric,C17414
1k,"R3,R4,R12",R_0805_2012Metric,C17513
4.7k,"R8,R9",R_0805_2012Metric,C17673
470,R5,R_0805_2012Metric,C17710
B5819W,D2,D_SOD-123,C8598
DS1307Z+,U2,SOIC-8_3.9x4.9mm_P1.27mm,C49375271 (MSKSEMI DS1307Z+MSK)
FLOW yellow-green,D4,LED_1206_3216Metric,C28310441
PUMP yellow,D3,LED_1206_3216Metric,C30584802
RELAY yellow,D7,LED_1206_3216Metric,C30584802
STATUS red,D5,LED_1206_3216Metric,C37635751
ULN2003A,U3,SOIC-16_3.9x9.9mm_P1.27mm,C7512
